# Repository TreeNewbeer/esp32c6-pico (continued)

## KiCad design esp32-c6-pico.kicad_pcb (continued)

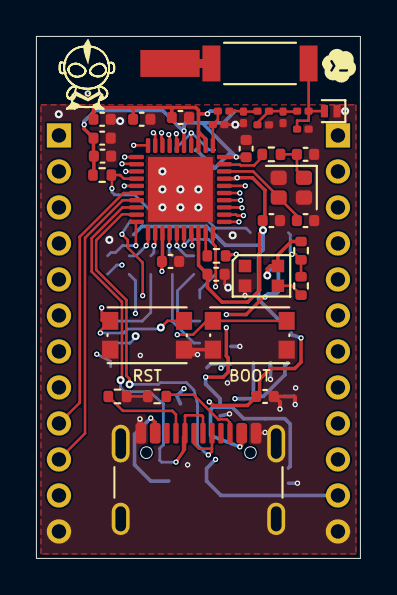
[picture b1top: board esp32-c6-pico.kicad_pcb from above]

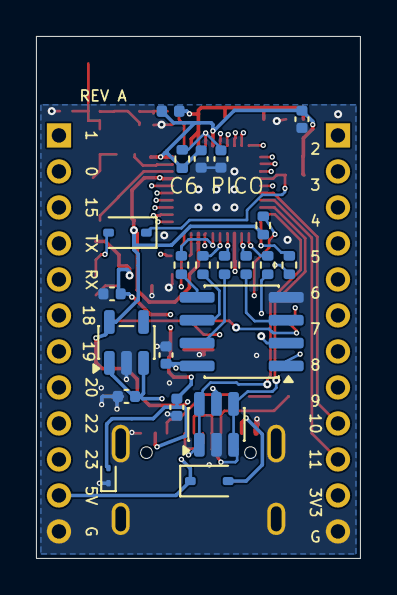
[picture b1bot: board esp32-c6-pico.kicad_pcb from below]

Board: 4 copper layers, 18.0 x 29.0 mm, 59 parts (24 on the bottom side), 54 nets.

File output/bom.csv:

Reference,Value,MPN,Footprint,Populate,Note
U1,ESP32-C6,ESP32-C6,Pico:QFN40_ESP32_C6_Compact,YES,"QFN40, NOT the pin-incompatible C6FH4 QFN32"
C3,1.5pF,1.5pF,Capacitor_SMD:C_0201_0603Metric,YES,"C0G; RF initial value, VNA tuning required"
L1,2.4nH,2.4nH,Inductor_SMD:L_0201_0603Metric,YES,High-Q RF; initial value
C2,1.5pF,1.5pF,Capacitor_SMD:C_0201_0603Metric,YES,C0G; RF initial value
C16,10pF,10pF,Capacitor_SMD:C_0201_0603Metric,YES,C0G DC-block / tuning initial value
L3,DNP,DNP,Inductor_SMD:L_0201_0603Metric,NO,Shunt RF tuning option
C17,DNP,DNP,Capacitor_SMD:C_0201_0603Metric,NO,Antenna pi input shunt
R6,0R,0R,Resistor_SMD:R_0201_0603Metric,YES,Antenna pi series tuning option
C18,DNP,DNP,Capacitor_SMD:C_0201_0603Metric,NO,Antenna pi output shunt
AE1,RFANT5220110A0T,RFANT5220110A0T,Walsin_Antenna:RFANT5220110A0T,YES,"Pad 2 stays open with axial end copper; right-aligned horizontal prototype, 20x3.8 mm all-layer clearance; RF validation required"
D1,PESD5V0F1BL-Q,PESD5V0F1BL-Q,Diode_SMD:D_SOD-882,NO,0.4 pF antenna ESD option; original 15 pF ESD9B is unsuitable
C8,10uF,10uF,Capacitor_SMD:C_0402_1005Metric,YES,"Main bulk; 0402, 10 V minimum; X5R reference; verify effective capacitance under DC bias"
C9,1uF,1uF,Capacitor_SMD:C_0402_1005Metric,YES,Main bulk; X7R 10 V minimum
C10,100nF,100nF,Capacitor_SMD:C_0402_1005Metric,YES,Main HF; X7R 10 V minimum
C12,100nF,100nF,Capacitor_SMD:C_0402_1005Metric,YES,U1 pin 5; X7R 10 V minimum
C13,100nF,100nF,Capacitor_SMD:C_0402_1005Metric,YES,U1 pin 28; X7R 10 V minimum
C14,100nF,100nF,Capacitor_SMD:C_0402_1005Metric,YES,U1 pin 37; X7R 10 V minimum
C15,100nF,100nF,Capacitor_SMD:C_0402_1005Metric,YES,U1 pin 40; X7R 10 V minimum
L2,2.0nH,2.0nH,Inductor_SMD:L_0402_1005Metric,YES,"RF supply filter; Irated >= 500 mA, low DCR"
C11,1uF,1uF,Capacitor_SMD:C_0402_1005Metric,YES,U1 pins 2/3 local bypass
C19,10uF,10uF,Capacitor_SMD:C_0402_1005Metric,YES,"U1 pin 2 local bulk; 0402, 10 V minimum; verify effective capacitance under DC bias"
C20,10uF,10uF,Capacitor_SMD:C_0402_1005Metric,YES,"U1 pin 3 local bulk; 0402, 10 V minimum; verify effective capacitance under DC bias"
U3,W25Q32JVSNIQ,W25Q32JVSNIQ,Package_SO:SOIC-8_3.9x4.9mm_P1.27mm,YES,"SOIC-8 150 mil; 3.9 x 4.9 mm body; no exposed pad; 4 MB, 2.7-3.6 V"
R17,0R,0R,Resistor_SMD:R_0402_1005Metric,YES,Place at U1; SPI clock defaults to 40 MHz for bring-up
R1,0R,0R,Resistor_SMD:R_0402_1005Metric,YES,Place at U1; SPI clock defaults to 40 MHz for bring-up
R2,0R,0R,Resistor_SMD:R_0402_1005Metric,YES,Place at U1; SPI clock defaults to 40 MHz for bring-up
R3,0R,0R,Resistor_SMD:R_0402_1005Metric,YES,Place at U1; SPI clock defaults to 40 MHz for bring-up
R4,0R,0R,Resistor_SMD:R_0402_1005Metric,YES,Place at U1; SPI clock defaults to 40 MHz for bring-up
R5,0R,0R,Resistor_SMD:R_0402_1005Metric,YES,Place at U1; SPI clock defaults to 40 MHz for bring-up
C6,100nF,100nF,Capacitor_SMD:C_0402_1005Metric,YES,At flash VCC
C7,1uF,1uF,Capacitor_SMD:C_0402_1005Metric,YES,At U1 VDD_SPI pin
R18,0R,0R,Resistor_SMD:R_0402_1005Metric,YES,Crystal series link; 0R per ESP32-C6-WROOM-1/1U v1.4 figs 8-1/8-2 (R4); former L4
Y1,40MHz / CL=8pF,E9X400081G08,Crystal:Crystal_SMD_2016-4Pin_2.0x1.6mm,YES,"Eaton E9X; 40 MHz, CL 8 pF, initial tolerance 10 ppm, ESR <=50 ohm; verify assembled frequency"
C4,12pF,12pF,Capacitor_SMD:C_0402_1005Metric,YES,C0G; assumes about 2 pF stray; trim frequency on hardware
C5,12pF,12pF,Capacitor_SMD:C_0402_1005Metric,YES,C0G; crystal load tuning
J1,USB4105-GF-A,USB4105-GF-A,Connector_USB:USB_C_Receptacle_GCT_USB4105-xx-A_16P_TopMnt_Horizontal,YES,
R10,5.1k,5.1k,Resistor_SMD:R_0402_1005Metric,YES,1%; one Rd per CC pin
R11,5.1k,5.1k,Resistor_SMD:R_0402_1005Metric,YES,"1%; USB-C sink, no PD"
D4,USBLC6-2SC6,USBLC6-2SC6,Package_TO_SOT_SMD:SOT-23-6,YES,
D3,ESD9B5.0ST5G,ESD9B5.0ST5G,Diode_SMD:D_SOD-923,YES,Move original 15 pF TVS to USB power rail
D5,BAT760-7,BAT760-7,Diode_SMD:D_SOD-323,YES,"Same part/package as at820_tiga D9/D10; 30 V, 1 A with datasheet thermal derating; blocks USB backfeed"
U2,AP2112K-3.3,AP2112K-3.3TRG1,Package_TO_SOT_SMD:SOT-23-5,YES,600 mA peak rating; continuous load limited by SOT25 dissipation
C22,10uF,10uF,Capacitor_SMD:C_0402_1005Metric,YES,"Regulator input; 0402, 10 V minimum; X5R reference; verify effective capacitance under DC bias"
C23,22uF,22uF,Capacitor_SMD:C_0402_1005Metric,YES,"Regulator output; 0402, 22 uF nominal, 10 V minimum; X5R reference; verify effective capacitance under DC bias"
C24,100nF,100nF,Capacitor_SMD:C_0402_1005Metric,YES,
R7,10k,10k,Resistor_SMD:R_0402_1005Metric,YES,
C21,1uF,1uF,Capacitor_SMD:C_0402_1005Metric,YES,
SW1,RESET,KMR221GLFS,Button_Switch_SMD:SW_Push_1P1T_NO_CK_KMR2,YES,
R8,10k,10k,Resistor_SMD:R_0402_1005Metric,YES,
SW2,BOOT,KMR221GLFS,Button_Switch_SMD:SW_Push_1P1T_NO_CK_KMR2,YES,
R9,3.3k,3.3k,Resistor_SMD:R_0402_1005Metric,YES,GPIO8 strapping pull-up; 3.3k to 3V3 per DevKitC-1 v1.4 R6
R14,499R,499R,Resistor_SMD:R_0402_1005Metric,YES,UART0 harmonic damping at U1
J2,J2 GPIO / 2.00mm,1x12 P2.00 vertical header,Pico:PinHeader_1x12_P2.00mm_Compact,YES,
J3,J3 GPIO / 2.00mm,1x12 P2.00 vertical header,Pico:PinHeader_1x12_P2.00mm_Compact,YES,
D6,1N4148WS,1N4148WS-7-F,Diode_SMD:D_SOD-323,YES,"Silicon switching diode level shift: cathode to GPIO8, anode to the pulled-up WS2812B data node"
R19,10k,10k,Resistor_SMD:R_0402_1005Metric,YES,WS2812B data pull-up to the USB 5 V rail
R15,0R,0R,Resistor_SMD:R_0402_1005Metric,YES,RGB data series link; 0R per DevKitC-1 v1.4 R17
D2,WS2812B-2020,WS2812B-2020,LED_SMD:LED_WS2812B-2020_PLCC4_2.0x2.0mm,YES,
C25,1uF,1uF,Capacitor_SMD:C_0402_1005Metric,YES,At RGB VDD

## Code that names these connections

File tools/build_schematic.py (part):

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def build():
    note('core', 'ESP32-C6 PICO | CORE, RF & FLASH | REV A', 20, 20, 2.54)
    note('core', '01  ESP32-C6 QFN40 - external 4 MB flash', 20, 42, 1.8)
    main = {1:'RF_CHIP',2:'V3A',3:'V3A',4:'CHIP_EN',5:'+3V3',6:'GPIO0',7:'GPIO1',8:'GPIO2',9:'GPIO3',
            10:'GPIO4',11:'GPIO5',12:'GPIO6',13:'GPIO7',14:'GPIO8',15:'GPIO9_BOOT',16:'GPIO10',17:'GPIO11',
            18:'USB_MCU_D-',19:'USB_MCU_D+',20:'SPI_CS_MCU',21:'SPI_Q_MCU',22:'SPI_WP_MCU',23:'VDD_SPI',
            24:'SPI_HD_MCU',25:'SPI_CLK_MCU',26:'SPI_D_MCU',27:'GPIO15',28:'+3V3',29:'U0TXD_MCU',30:'U0RXD',
            31:'GPIO18',32:'GPIO19',33:'GPIO20',34:'GPIO21_LED',35:'GPIO22',36:'GPIO23',37:'+3V3',38:'XTAL_N',39:'XTAL_P',40:'+3V3',41:'GND'}
    part('U1','espressif-kicad-addon:ESP32-C6','ESP32-C6',
         'Pico:QFN40_ESP32_C6_Compact',main,88.9,105.41,detail='QFN40, NOT the pin-incompatible C6FH4 QFN32')
    note('core', '02  RF chip CLCCL filter + antenna pi network', 162, 42, 1.8)
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    for i,(ref,val,net,fp,msg) in enumerate(caps):
        passive(ref,val,net,'GND',171+i*30,132,fp=fp,note=msg+'; X7R 10 V minimum')
    passive('L2','2.0nH','+3V3','V3A',177,166,angle=90,fp='Inductor_SMD:L_0402_1005Metric',note='RF supply filter; Irated >= 500 mA, low DCR')
    passive('C11','1uF','V3A','GND',214,166,note='U1 pins 2/3 local bypass')
    passive('C19','10uF','V3A','GND',246,166,fp=C0402,note='U1 pin 2 local bulk')
    passive('C20','10uF','V3A','GND',278,166,fp=C0402,note='U1 pin 3 local bulk')
    note('core','04  Quad-SPI flash, powered from U1 VDD_SPI',20,158,1.8)
    flashnets={1:'SPI_CS',2:'SPI_Q',3:'SPI_WP',4:'GND',5:'SPI_D',6:'SPI_CLK',7:'SPI_HD',8:'VDD_SPI'}
    flashnets[9]='GND'
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    passive('C21','1uF','CHIP_EN','GND',54,174,sheet='io')
    part('SW1','Switch:SW_Push','RESET','Button_Switch_SMD:SW_Push_1P1T_NO_CK_KMR2',
         {1:'CHIP_EN',2:'GND'},86,180,sheet='io',mpn='KMR221GLFS')
    passive('R8','10k','+3V3','GPIO9_BOOT',119,174,sheet='io')
    part('SW2','Switch:SW_Push','BOOT','Button_Switch_SMD:SW_Push_1P1T_NO_CK_KMR2',
         {1:'GPIO9_BOOT',2:'GND'},151,180,sheet='io',mpn='KMR221GLFS')
    passive('R9','10k','+3V3','GPIO8',188,174,sheet='io')
    passive('R14','499R','U0TXD_MCU','U0TXD',71,207,angle=90,sheet='io',note='UART0 harmonic damping at U1')
    note('io','Download strap: GPIO8=1, GPIO9=0.\nHold BOOT, tap RESET, release BOOT.\nUART adapter: 3.3 V logic only; TX/RX cross-connect.',20,237)

    note('io','09  2 mm pitch GPIO headers',242,155,1.8)
    left=['GND','+3V3','GPIO0','GPIO1','GPIO2','GPIO3','GPIO4','GPIO5','GPIO6','GPIO7','GPIO8','GPIO9_BOOT']
    right=['+5V','GND','GPIO10','GPIO11','GPIO15','U0TXD','U0RXD','GPIO18','GPIO19','GPIO20','GPIO22','GPIO23']
    for ref,nets,x in [('J2',left,274),('J3',right,371)]:
        part(ref,'Connector_Generic:Conn_01x12',ref+' GPIO / 2.00mm',
             'Pico:PinHeader_1x12_P2.00mm_Compact',
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    note('io','10  RGB indicator - 5 V logic buffer',20,260,1.8)
    # Use a third sheet-sized row on A3; enough horizontal spacing for buffer symbol.
    part('U4','Pico_Custom:SN74LV1T125','SN74LV1T125','Package_TO_SOT_SMD:SOT-23-5',
         {1:'GND',2:'GPIO21_LED',3:'GND',4:'LED_DATA_5V',5:'VBUS_USB'},89,278,sheet='io',mpn='SN74LV1T125DBVR')
    passive('R16','100k','GPIO21_LED','GND',37,279,sheet='io',note='Keep LED data low at reset')
    passive('R15','330R','LED_DATA_5V','LED_DIN',145,273,angle=90,sheet='io')
    part('D2','LED:WS2812B-2020','WS2812B-2020','Pico:WS2812B_2020_Compact',
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
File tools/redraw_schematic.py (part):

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                 ('C16',336.55,50.8,90),('L3',361.95,63.5,0),('C17',387.35,63.5,0),
                 ('R6',412.75,50.8,90),('C18',438.15,63.5,0),('D1',463.55,63.5,90),('AE1',495.3,43.18,0)]:symbol(ref,x,y,a)
line('core','RF_CHIP',P('U1',1),(241.3,50.8),P('L1',1))
line('core','RF_CHIP',(260.35,50.8),P('C3',1));netlabel('core','RF_CHIP',247.65,50.8)
line('core','RF_MID',P('L1',2),P('C16',1));line('core','RF_MID',(311.15,50.8),P('C2',1));netlabel('core','RF_MID',304.8,50.8)
line('core','RF_50',P('C16',2),P('R6',1))
for ref in ['L3','C17']:line('core','RF_50',(P(ref,1)[0],50.8),P(ref,1))
netlabel('core','RF_50',374.65,50.8)
line('core','ANT_FEED',P('R6',2),P('AE1',1));line('core','ANT_FEED',(438.15,50.8),P('C18',1))
line('core','ANT_FEED',(P('D1',2)[0],50.8),P('D1',2));netlabel('core','ANT_FEED',481.33,50.8)
for ref,n in [('C3',2),('C2',2),('L3',2),('C17',2),('C18',2),('D1',1)]:ground('core',P(ref,n))

text('core','3V3 bulk and VDDA3P3 filtering',53.34,100.33,1.778)
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line('core','V3A',P('L2',2),(210.82,114.3),(210.82,132.08),P('U1',3))
line('core','V3A',(210.82,121.92),P('U1',2))
for ref in ['C19','C20','C11']:line('core','V3A',(P(ref,1)[0],114.3),P(ref,1));ground('core',P(ref,2))
netlabel('core','V3A',190.5,114.3)
for ref,pin,y in [('C12',5,157.48),('C13',28,177.8),('C14',37,198.12),('C15',40,218.44)]:
    symbol(ref,195.58,y+5.08);line('core','+3V3',(175.26,y),P('U1',pin));line('core','+3V3',(195.58,y),P(ref,1))
    line('core','+3V3',(175.26,y),(175.26,y-5.08));power('core','+3V3',(175.26,y-5.08));ground('core',P(ref,2))
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text('core','EN delay and RESET',96.52,226.06,1.778)
symbol('R7',175.26,233.68);symbol('C21',187.96,248.92);symbol('SW1',154.94,248.92,270)
line('core','CHIP_EN',P('U1',4),(154.94,241.3),P('SW1',1));line('core','CHIP_EN',P('R7',2),(175.26,241.3));line('core','CHIP_EN',(187.96,241.3),P('C21',1))
power('core','+3V3',P('R7',1));ground('core',P('C21',2));ground('core',P('SW1',2));netlabel('core','CHIP_EN',207.01,241.3)
nc('core',P('U1',34))  # GPIO21 is unused; GPIO8 drives RGB on the right.
text('core','BOOT: GPIO8 high, GPIO9 low at reset',96.52,269.24,1.524)
symbol('R8',175.26,274.32);symbol('SW2',187.96,289.56,270)
line('core','GPIO9_BOOT',P('R8',2),(175.26,281.94),P('U1',15));line('core','GPIO9_BOOT',(187.96,281.94),P('SW2',1))
power('core','+3V3',P('R8',1));ground('core',P('SW2',2));glabel('core','GPIO9_BOOT',210.82,281.94,180)

text('core','40 MHz crystal / local load capacitors',91.44,302.26,1.778)
symbol('R18',193.04,309.88,270);symbol('Y1',160.02,320.04);symbol('C4',139.7,325.12);symbol('C5',187.96,335.28)
line('core','XTAL_P',P('U1',39),P('R18',1));netlabel('core','XTAL_P',210.82,309.88)
line('core','XTAL_LOAD_P',P('R18',2),(147.32,309.88),(147.32,320.04),P('Y1',1))
line('core','XTAL_LOAD_P',(147.32,320.04),(139.7,320.04),P('C4',1));netlabel('core','XTAL_LOAD_P',162.56,309.88)
line('core','XTAL_N',P('U1',38),(177.8,330.2),(177.8,320.04),P('Y1',3));line('core','XTAL_N',(187.96,330.2),P('C5',1));netlabel('core','XTAL_N',210.82,330.2)
ground('core',P('C4',2));ground('core',P('C5',2));ground('core',P('Y1',2));ground('core',P('U1',41))

text('core','4 MB QSPI flash / series resistors at U1',327.66,78.74,1.778)
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text('core','Native USB Serial/JTAG / connector and TVS on sheet 2',327.66,154.94,1.778)
for n,y,x,net in [(18,165.1,336.55,'USB_D-'),(19,185.42,335.28,'USB_D+')]:
    line('core',net,P('U1',n),(x,y));glabel('core',net,x,y,0)
symbol('R14',370.84,213.36,90);line('core','U0TXD_MCU',P('U1',29),P('R14',1));line('core','U0TXD',P('R14',2),(400.05,213.36));glabel('core','U0TXD',400.05,213.36,0);glabel('core','U0TXD_MCU',322.58,213.36,180)
line('core','U0RXD',P('U1',30),(400.05,223.52));glabel('core','U0RXD',400.05,223.52,0)
symbol('R9',391.16,231.14);symbol('D6',416.56,241.3);symbol('R15',457.2,241.3,90);symbol('D2',502.92,241.3)
symbol('R19',441.96,228.6);symbol('C25',528.32,228.6)
line('core','GPIO8',P('U1',14),P('D6',1));glabel('core','GPIO8',322.58,241.3,180)
line('core','GPIO8',P('R9',2),(391.16,241.3));power('core','+3V3',P('R9',1))
line('core','LED_DATA_5V',P('D6',2),P('R15',1));line('core','LED_DATA_5V',P('R19',2),(441.96,241.3));glabel('core','LED_DATA_5V',433.07,241.3,180)
line('core','LED_DIN',P('R15',2),P('D2',3));glabel('core','LED_DIN',482.6,241.3,0)
line('core','VBUS_USB',(416.56,220.98),(528.32,220.98),P('C25',1))
line('core','VBUS_USB',(441.96,220.98),P('R19',1));line('core','VBUS_USB',(502.92,220.98),P('D2',4));power('core','VBUS_USB',(416.56,220.98))
ground('core',P('C25',2));ground('core',P('D2',2))
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        q=P(ref,n);end=(q[0]-15.24,q[1]);line('io',net,q,end)
        if net in ['GND','+3V3','+5V']:glabel('io',net,*end,180)
        else:glabel('io',net,*end,180)
text('io','Keep GPIO4/5/8/9/15 strap levels valid during reset.\nHold BOOT, tap RESET, then release BOOT for recovery.\nUART adapter logic must be 3.3 V.',35.56,228.6,1.524)
for i,net in [(0,'GND'),(1,'VBUS_USB'),(3,'+5V'),(4,'V3A')]:
    ref=f'#FLG{i:02d}';symbol(ref,254+i*25.4,175.26,sheet='io');q=P(ref,1);line('io',net,q,(q[0],q[1]+5.08));glabel('io',net,q[0],q[1]+5.08,270)
assert set(PARTS)<=PLACED,set(PARTS)-PLACED
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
